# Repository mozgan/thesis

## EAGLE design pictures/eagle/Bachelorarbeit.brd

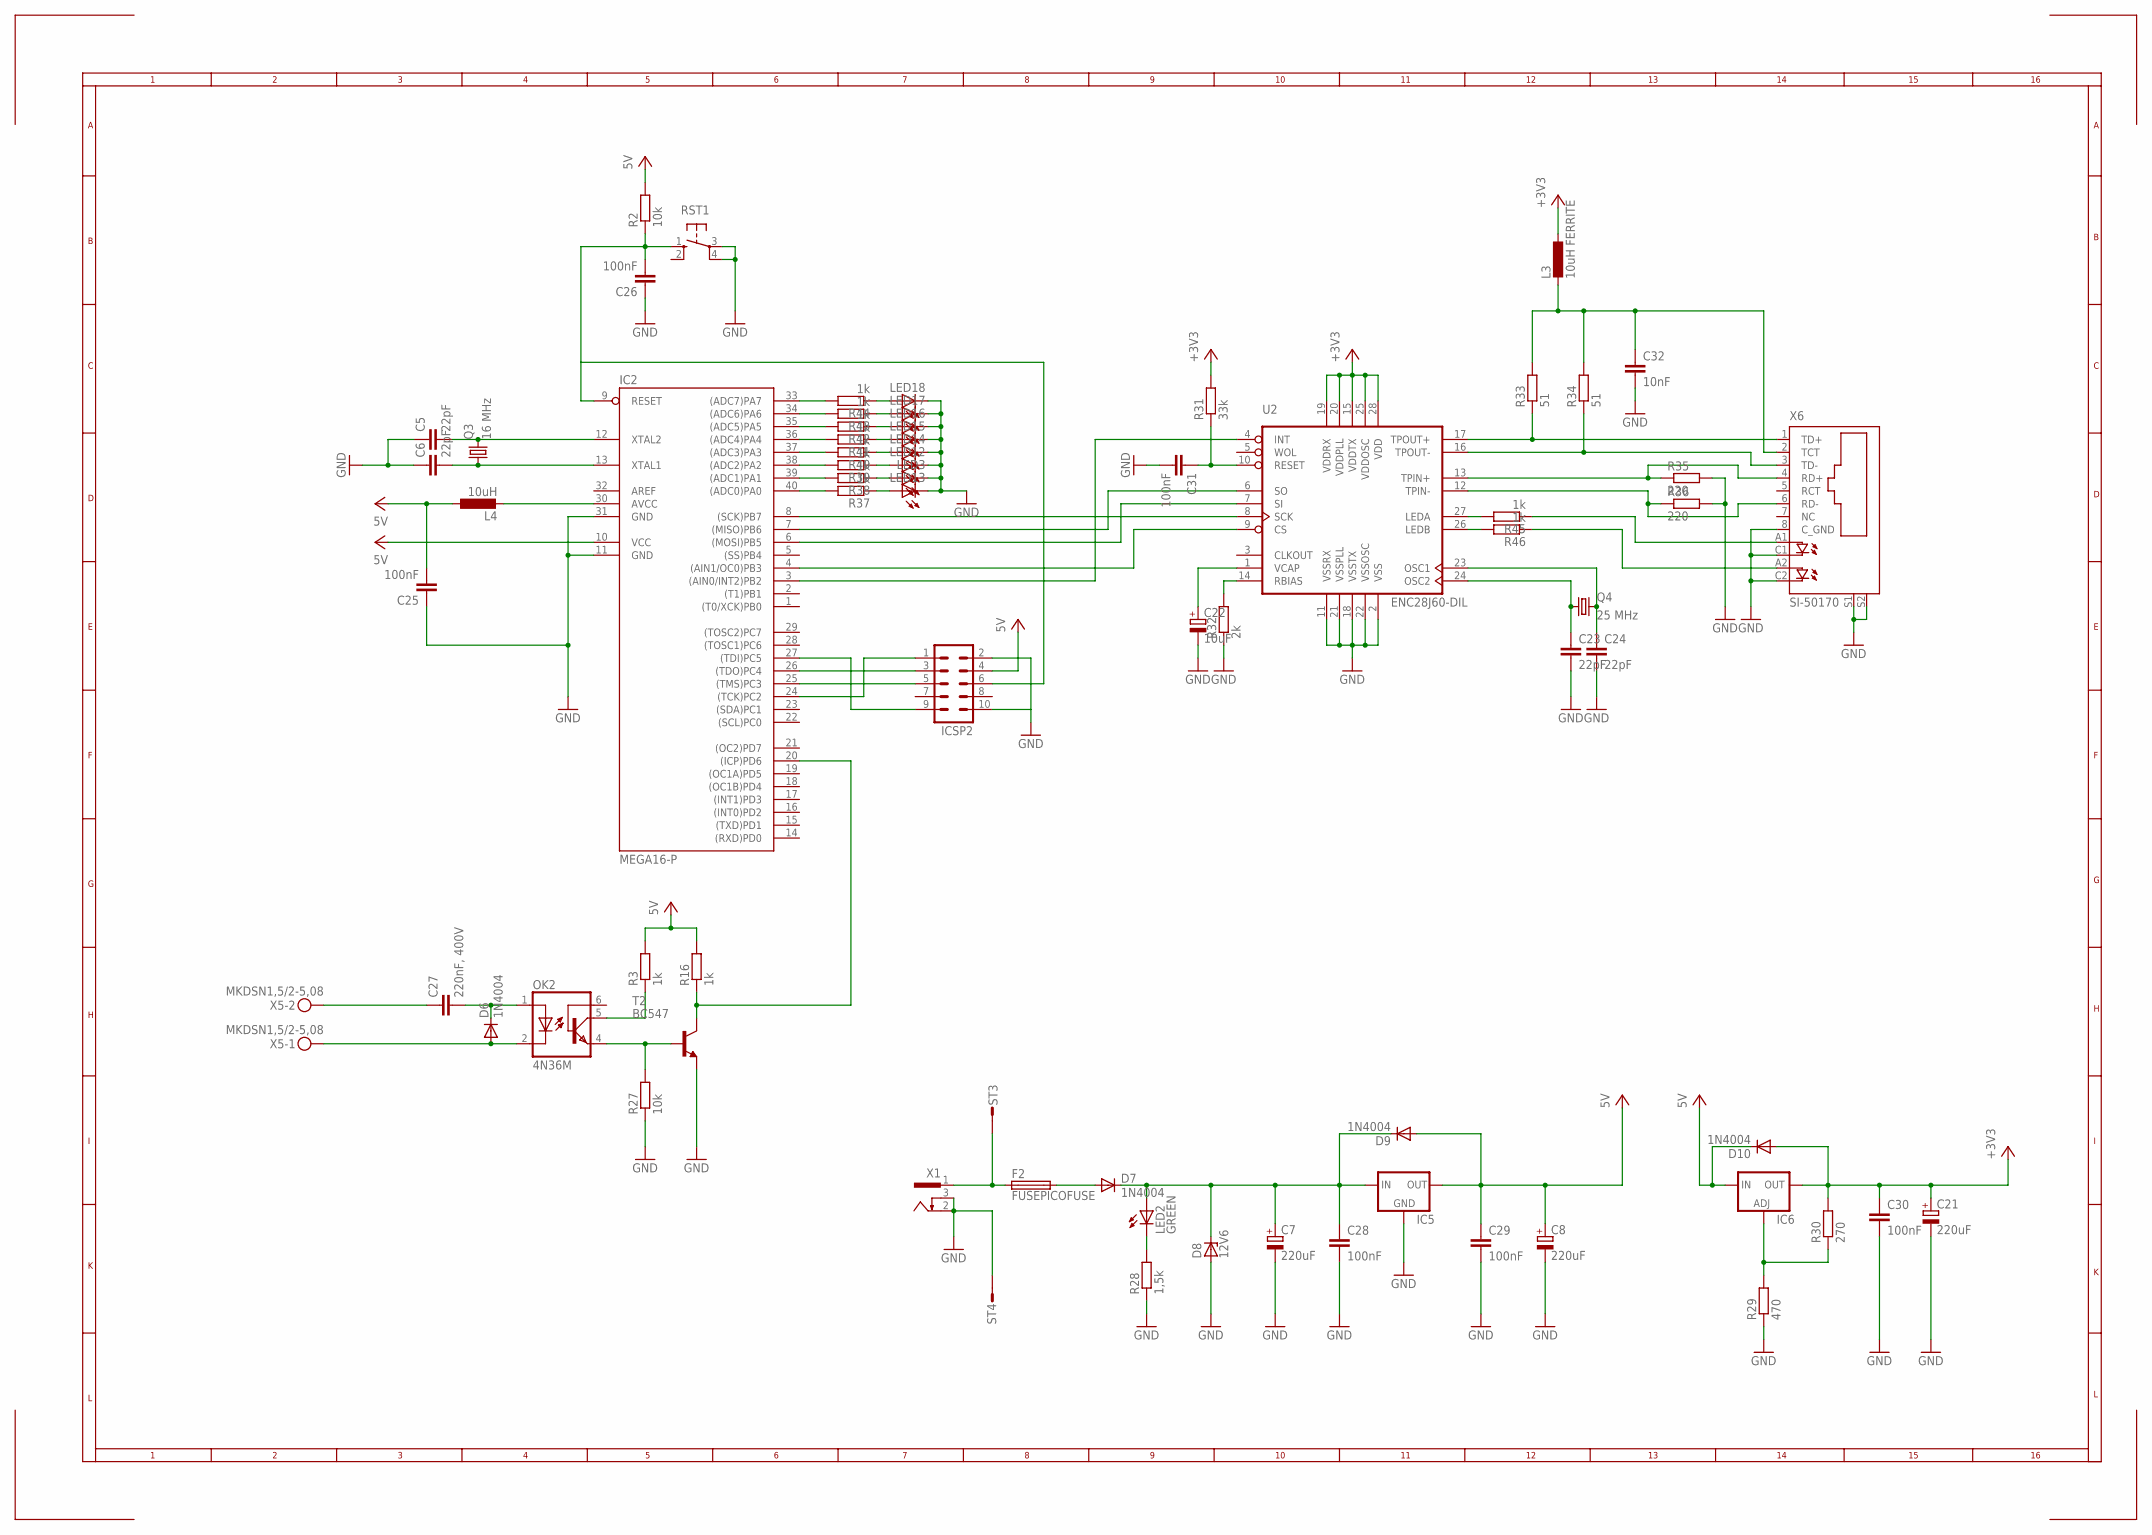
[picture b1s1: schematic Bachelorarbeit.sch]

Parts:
C5, C6, C23, C24: 22pF; C025-024X044
C7, C8, C21: 220uF; E3,5-8
C22: 10uF; E3,5-8
C25, C26, C28, C29, C30, C31: 100nF; C025-025X050
C27: 220nF, 400V; C025-025X050
C32: 10nF; C025-025X050
D6, D7, D9, D10: 1N4004; DO41-10
D8: 12V6; DO34Z7
F2: FUSEPICOFUSE; PICOFUSE
IC2: MEGA16-P; DIL40
IC5: 78XXS
IC6: LM317TS; 317TS
ICSP2: 10V
L3: 10uH FERRITE; 0204/5
L4: 10uH; 0204/5
LED2: GREEN; LED3MM
LED3, LED12, LED13, LED14, LED15, LED16, LED17, LED18: LED3MM
OK2: 4N36M; DIL06
Q3: 16 MHz; HC49U-V
Q4: 25 MHz; HC49U-V
R2, R27: 10k; 0207/10
R3, R16, R37, R38, R39, R40, R41, R42, R43, R44, R45, R46: 1k; 0207/10
R28: 1,5k; 0207/10
R29: 470; 0207/10
R30: 270; 0207/10
R31: 33k; 0207/10
R32: 2k; 0207/10
R33, R34: 51; 0207/10
R35, R36: 220; 0207/10
RST1: 10-XX; B3F-10XX
ST3, ST4: ST2,8
T2: BC547; TO92
U2: ENC28J60-DIL; DIL28-3
X1: SCD-014A; SCD-014-A
X5: MKDSN1,5/2-5,08
X6: SI-50170

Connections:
GND: C5.1, C6.1, C7.-, C8.-, C21.-, C22.-, C23.2, C24.2, C25.1, C26.1, C28.2, C29.2, C30.2, C31.2, C32.2, D8.A, IC2.11 (GND), IC2.31 (GND), IC5.GND, ICSP2.2, ICSP2.10, LED3.K (C), LED12.K (C), LED13.K (C), LED14.K (C), LED15.K (C), LED16.K (C), LED17.K (C), LED18.K (C), R27.1, R28.1, R29.1, R32.1, R35.2, R36.2, RST1.3, RST1.4 (P1), ST4.1, T2.1 (E), U2.2 (VSS), U2.11 (VSSRX), U2.18 (VSSTX), U2.21 (VSSPLL), U2.22 (VSSOSC), X1.2, X1.3, X6.8 (C_GND), X6.C1 (C), X6.C2 (C1), X6.S1, X6.S2
unnamed: C6.2, IC2.13 (XTAL1), Q3.1
unnamed: C5.2, IC2.12 (XTAL2), Q3.2
unnamed: C26.2, IC2.9 (RESET), ICSP2.6, R2.1, RST1.1 (S)
unnamed: D6.A, OK2.2 (C), X5.1
unnamed: C27.2, D6.C, OK2.1 (A)
unnamed: OK2.4 (EMI), R27.2, T2.2 (B)
unnamed: OK2.5 (COL), R3.1
unnamed: IC2.20 ((ICP)PD6), R16.1, T2.3 (C)
unnamed: F2.1, ST3.1, X1.1
unnamed: D7.A, F2.2
unnamed: C7.+, C28.1, D7.C, D8.C, D9.C, IC5.IN, LED2.A
unnamed: LED2.K (C), R28.2
unnamed: IC6.1 (ADJ), R29.2, R30.1
unnamed: IC2.3 ((AIN0/INT2)PB2), U2.4 (INT)
unnamed: C31.1, R31.1, U2.10 (RESET)
unnamed: IC2.7 ((MISO)PB6), U2.6 (SO)
unnamed: IC2.6 ((MOSI)PB5), U2.7 (SI)
unnamed: IC2.8 ((SCK)PB7), U2.8 (SCK)
unnamed: IC2.4 ((AIN1/OC0)PB3), U2.9 (CS)
unnamed: C22.+, U2.1 (VCAP)
unnamed: R32.2, U2.14 (RBIAS)
unnamed: IC2.30 (AVCC), L4.2
unnamed: LED18.A, R44.1
unnamed: LED17.A, R43.1
unnamed: LED16.A, R42.1
unnamed: LED15.A, R41.1
unnamed: LED14.A, R40.1
unnamed: LED12.A, R39.1
unnamed: LED3.A, R38.1
unnamed: LED13.A, R37.1
unnamed: C23.1, Q4.1, U2.24 (OSC2)
unnamed: C24.1, Q4.2, U2.23 (OSC1)
unnamed: C27.1, X5.2
unnamed: R35.1, U2.13 (TPIN+), X6.4 (RD+)
unnamed: R36.1, U2.12 (TPIN-), X6.6 (RD-)
unnamed: R45.2, U2.27 (LEDA)
unnamed: R45.1, X6.A1 (A)
unnamed: R46.2, U2.26 (LEDB)
unnamed: R46.1, X6.A2 (A1)
unnamed: R34.1, U2.16 (TPOUT-), X6.3 (TD-)
unnamed: R33.1, U2.17 (TPOUT+), X6.1 (TD+)
unnamed: C32.1, L3.2, R33.2, R34.2, X6.2 (TCT)
unnamed: IC2.33 ((ADC7)PA7), R44.2
unnamed: IC2.34 ((ADC6)PA6), R43.2
unnamed: IC2.35 ((ADC5)PA5), R42.2
unnamed: IC2.36 ((ADC4)PA4), R41.2
unnamed: IC2.37 ((ADC3)PA3), R40.2
unnamed: IC2.38 ((ADC2)PA2), R39.2
unnamed: IC2.39 ((ADC1)PA1), R38.2
unnamed: IC2.40 ((ADC0)PA0), R37.2
unnamed: IC2.24 ((TCK)PC2), ICSP2.1
unnamed: IC2.26 ((TDO)PC4), ICSP2.3
unnamed: IC2.25 ((TMS)PC3), ICSP2.5
unnamed: IC2.27 ((TDI)PC5), ICSP2.9
VCC: C8.+, C21.+, C25.2, C29.1, C30.1, D9.A, D10.A, D10.C, IC2.10 (VCC), IC5.OUT, IC6.2 (OUT), IC6.3 (IN), ICSP2.4, L3.1, L4.1, R2.2, R3.2, R16.2, R30.2, R31.2, U2.15 (VDDTX), U2.19 (VDDRX), U2.20 (VDDPLL), U2.25 (VDDOSC), U2.28 (VDD)

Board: 2 copper layers, 71 parts (0 on the bottom side), 56 nets, no tracks yet.

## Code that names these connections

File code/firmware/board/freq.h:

/*-
 * Copyright (c) 2013, mozgan.
 * All Rights Reserved with BSD License.
 * Read LICENSE file.
 */

/**
 * @file	freq.h
 * @brief	pin locations for "Frequenzmessung-Board"
 *
 * @author	M. Ozgan, <mozgan@mozgan.org>
 * @version	0.2
 * @date	19.08.2013 15:13:45
 * @internal
 *	$Compiler:	gcc (on Mac, GNU/Linux and 4.4BSD) $
 *	$Company:	TU Wien $
 *
 *  @bug	none
 *  @todo	none
 */

/*
 *	@(#) board/freq.h		TU Wien 19.08.2013
 *  $Id: freq.h,v 0.2 19.08.2013 15:13:45 mozgan Exp $
 */

#ifndef __FREQ_H__
#define __FREQ_H__  1

#include <device/atmega16.h>

/* LEDs for debuging */
#define	    LED_DDR	    DDRA
#define	    LED_PORT	    PORTA
#define	    LED_PIN	    PINA

#define	    LED0	    PA0
#define	    LED1	    PA1
#define	    LED2	    PA2
#define	    LED3	    PA3
#define	    LED4	    PA4
#define	    LED5	    PA5
#define	    LED6	    PA6
#define	    LED7	    PA7

#define	    LED_ALL	    0xFF
#define	    LED_OFF	    0x00

/* SPI */
#define	    SPI_DDR	    DDRB
#define	    SPI_PORT	    PORTB
#define	    SPI_SS	    PB4
#define	    SPI_MOSI	    PB5
#define	    SPI_MISO	    PB6
#define	    SPI_SCK	    PB7

/* ENC28J60 */
#define	    ENC_CTRL_DDR    DDRB
#define	    ENC_CTRL_PORT   PORTB
#define	    ENC_CTRL_CS	    PB3



#endif /* __FREQ_H__ */

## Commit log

2015-01-29 Bachelorarbeit
